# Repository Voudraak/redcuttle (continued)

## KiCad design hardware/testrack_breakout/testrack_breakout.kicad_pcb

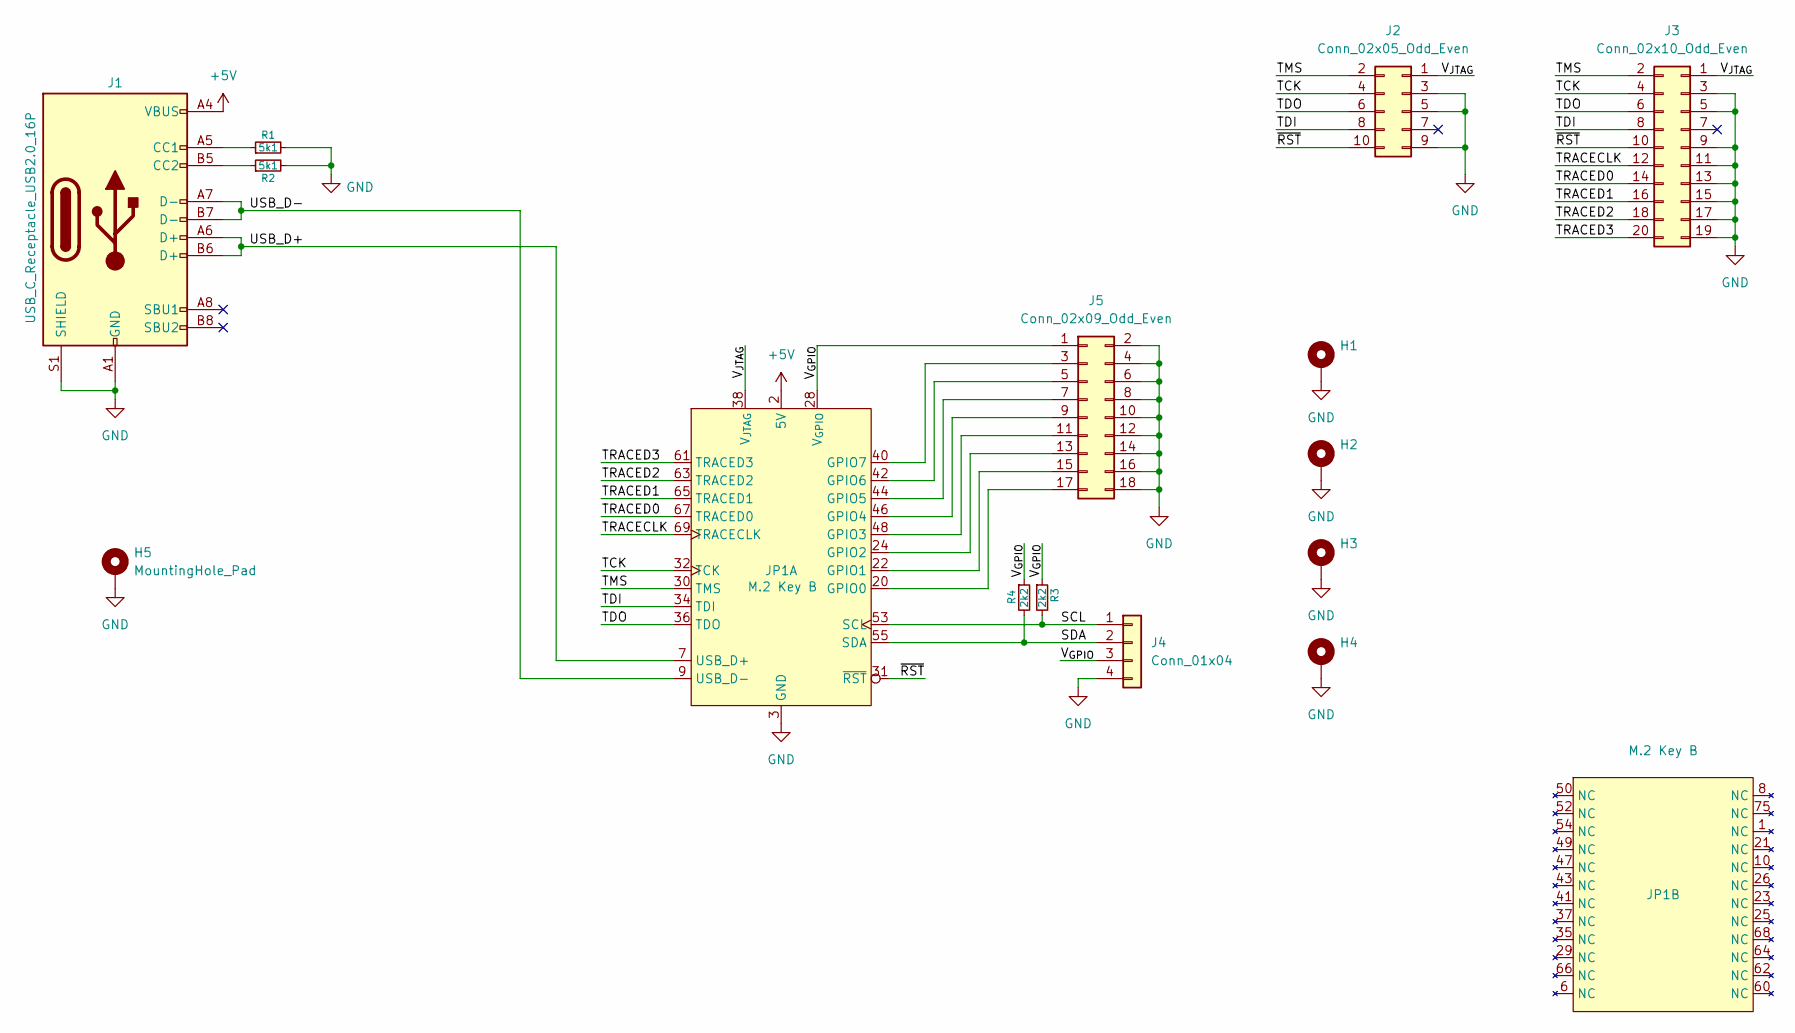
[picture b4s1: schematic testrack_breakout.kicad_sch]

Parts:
H1, H2, H3, H4: MountingHole_Pad; MountingHole_3.2mm_M3_Pad
H5: MountingHole_Pad; M2_MountingPost
J1: USB_C_Receptacle_USB2.0_16P; USB_C_Receptacle_HRO_TYPE-C-31-M-12; MPN_LCSC TYPE-C-31-M-12
J2: Conn_02x05_Odd_Even; PinHeader_2x05_P1.27mm_Vertical_SMD; MPN_FARNELL FTSH-105-01-L-DV-K-TR
J3: Conn_02x10_Odd_Even; PinHeader_2x10_P1.27mm_Vertical_SMD; MPN_FARNELL M50-3611042R
J4: Conn_01x04; JST_SH_SM04B-SRSS-TB_1x04-1MP_P1.00mm_Horizontal; MPN_FARNELL SM04B-SRSS-TB(LF)(SN)
J5: Conn_02x09_Odd_Even; PinHeader_2x09_P2.54mm_Vertical; MPN_FARNELL M20-9760942
JP1: M.2 Key B; TE_2199230-7_67_P0.5mm_Horizontal; MPN_LCSC SM3ZS067U410ABR1000
R1, R2: 5k1; R0603; MPN_FARNELL MCWR06X5101FTL
R3, R4: 2k2; R0603; MPN_FARNELL ERJU03F2201V

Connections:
+5V: J1.A4 (VBUS), J1.A9 (VBUS), J1.B4 (VBUS), J1.B9 (VBUS), JP1.2 (5V), JP1.4 (5V), JP1.70 (5V), JP1.72 (5V), JP1.74 (5V)
/SCL: J4.1, JP1.53 (SCL), R3.2
/SDA: J4.2, JP1.55 (SDA), R4.2
/TCK: J2.4, J3.4, JP1.32 (TCK)
/TDI: J2.8, J3.8, JP1.34 (TDI)
/TDO: J2.6, J3.6, JP1.36 (TDO)
/TMS: J2.2, J3.2, JP1.30 (TMS)
/TRACECLK: J3.12, JP1.69 (TRACECLK)
/TRACED0: J3.14, JP1.67 (TRACED0)
/TRACED1: J3.16, JP1.65 (TRACED1)
/TRACED2: J3.18, JP1.63 (TRACED2)
/TRACED3: J3.20, JP1.61 (TRACED3)
/USB_D+: J1.A6 (D+), J1.B6 (D+), JP1.7 (USB_D+)
/USB_D-: J1.A7 (D-), J1.B7 (D-), JP1.9 (USB_D-)
/V_{GPIO}: J4.3, J5.1, JP1.28 (V_{GPIO}), R3.1, R4.1
/V_{JTAG}: J2.1, J3.1, JP1.38 (V_{JTAG})
/~RST: J2.10, J3.10, JP1.31 (~RST)
GND: H1.1, H2.1, H3.1, H4.1, H5.1, J1.A1 (GND), J1.A12 (GND), J1.B1 (GND), J1.B12 (GND), J1.S1 (SHIELD), J2.3, J2.5, J2.9, J3.3, J3.5, J3.9, J3.11, J3.13, J3.15, J3.17, J3.19, J4.4, J5.2, J5.4, J5.6, J5.8, J5.10, J5.12, J5.14, J5.16, J5.18, JP1.3 (GND), JP1.5 (GND), JP1.11 (GND), JP1.27 (GND), JP1.33 (GND), JP1.39 (GND), JP1.45 (GND), JP1.51 (GND), JP1.57 (GND), JP1.71 (GND), JP1.73 (GND), R1.2, R2.2
unnamed: J1.A5 (CC1), R1.1
unnamed: J1.B5 (CC2), R2.1
unnamed: J5.3, JP1.40 (GPIO7)
unnamed: J5.5, JP1.42 (GPIO6)
unnamed: J5.7, JP1.44 (GPIO5)
unnamed: J5.9, JP1.46 (GPIO4)
unnamed: J5.11, JP1.48 (GPIO3)
unnamed: J5.13, JP1.24 (GPIO2)
unnamed: J5.15, JP1.22 (GPIO1)
unnamed: J5.17, JP1.20 (GPIO0)

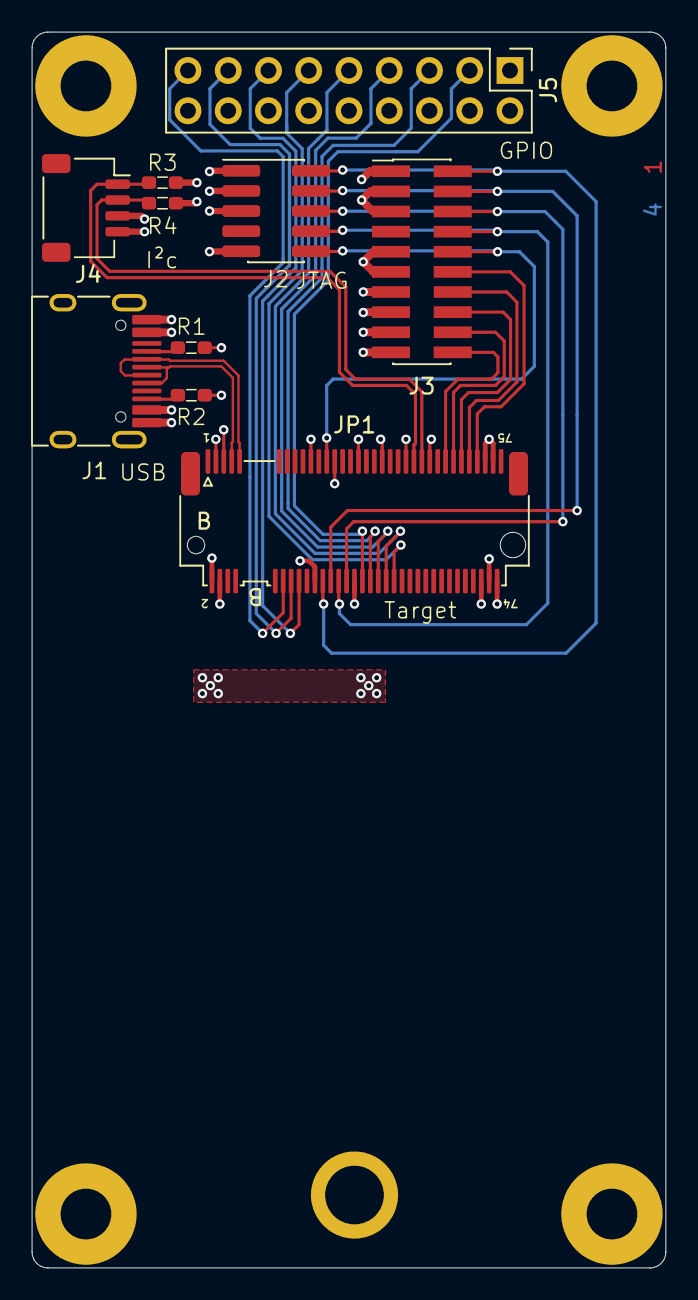
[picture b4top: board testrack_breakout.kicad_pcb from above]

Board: 4 copper layers, 40.0 x 78.0 mm, 15 parts (0 on the bottom side), 28 nets.

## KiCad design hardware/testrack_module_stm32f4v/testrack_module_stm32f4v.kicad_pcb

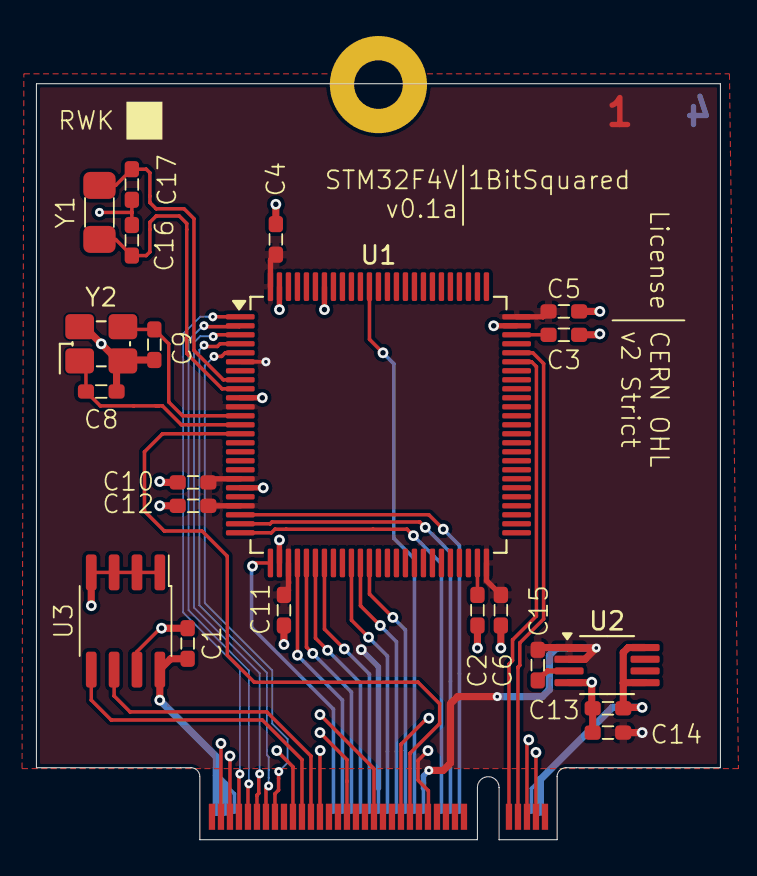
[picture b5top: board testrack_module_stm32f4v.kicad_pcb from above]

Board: 4 copper layers, 38.0 x 42.0 mm, 23 parts (0 on the bottom side), 28 nets.

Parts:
C1, C4, C5, C6, C10, C11, C12: 100n; C0603
C2, C3: 2.2u; C0603
C8, C9: 10p; C0603
C13, C14, C15: 22uF; C0603
C16, C17: 22p; C0603
H1: MountingHole_Pad; MountingHole_2.7mm_M2.5_Pad
J1: Bus_M.2_Socket_B; NGFF_B
U1: STM32F407VGTx; LQFP-100_14x14mm_P0.5mm
U2: LT1962-3.3; MSOP-8_3x3mm_P0.65mm
U3: 24AA01-I/SN; SO-8_3.9x4.9mm_P1.27mm
Y1: 32.768kHz; SMD3215
Y2: 12MHz; SMD3225

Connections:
+3.3V: C4.1, C5.1, C6.1, C10.1, C11.1, C12.1, C14.1, C15.2, J1.28 (V_{GPIO}), J1.38 (V_{JTAG}), U1.6 (VBAT), U1.11 (VDD), U1.19 (VDD), U1.22 (VDDA), U1.28 (VDD), U1.50 (VDD), U1.75 (VDD), U1.100 (VDD), U2.1 (OUT), U2.2 (SENSE)
+5V: C1.1, C13.1, J1.2 (5V), J1.4 (5V), J1.70 (5V), J1.72 (5V), J1.74 (5V), U2.5 (~SHDN), U2.8 (IN), U3.8 (VCC)
/GPIO0: J1.20 (GPIO0), U1.23 (PA0)
/GPIO1: J1.22 (GPIO1), U1.24 (PA1)
/GPIO2: J1.24 (GPIO2), U1.25 (PA2)
/GPIO3: J1.48 (GPIO3), U1.26 (PA3)
/GPIO4: J1.46 (GPIO4), U1.29 (PA4)
/GPIO5: J1.44 (GPIO5), U1.30 (PA5)
/GPIO6: J1.42 (GPIO6), U1.31 (PA6)
/GPIO7: J1.40 (GPIO7), U1.32 (PA7)
/SCL: J1.53 (SCL), U3.6 (SCL)
/SDA: J1.55 (SDA), U3.5 (SDA)
/TRACECLK: J1.69 (TRACECLK), U1.1 (PE2)
/TRACED0: J1.67 (TRACED0), U1.2 (PE3)
/TRACED1: J1.65 (TRACED1), U1.3 (PE4)
/TRACED2: J1.63 (TRACED2), U1.4 (PE5)
/TRACED3: J1.61 (TRACED3), U1.5 (PE6)
/USB_D+: J1.7 (USB_D+), U1.71 (PA12)
/USB_D-: J1.9 (USB_D-), U1.70 (PA11)
/~RST: J1.31 (~RST), U1.14 (NRST)
GND: C1.2, C2.2, C3.2, C4.2, C5.2, C6.2, C8.2, C9.2, C10.2, C11.2, C12.2, C13.2, C14.2, C16.2, C17.2, H1.1, J1.3 (GND), J1.5 (GND), J1.27 (GND), J1.33 (GND), J1.39 (GND), J1.45 (GND), J1.51 (GND), J1.57 (GND), J1.71 (GND), J1.73 (GND), U1.10 (VSS), U1.20 (VSSA), U1.27 (VSS), U1.74 (VSS), U1.94 (BOOT0), U1.99 (VSS), U2.4 (GND), U3.1 (A0), U3.2 (A1), U3.3 (A2), U3.4 (GND), U3.7 (WP), Y2.2, Y2.4
unnamed: C17.1, U1.8 (PC14), Y1.2
unnamed: C16.1, U1.9 (PC15), Y1.1
unnamed: C9.1, U1.12 (RCC_OSC_IN), Y2.3
unnamed: C8.1, U1.13 (RCC_OSC_OUT), Y2.1
unnamed: C2.1, U1.49 (VCAP_1)
unnamed: C3.1, U1.73 (VCAP_2)
unnamed: C15.1, U2.3 (BYP)

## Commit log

2025-08-28 Built a schematic for the stm32f4v target board
2025-09-13 Laid out and routed the testrack_module_stm32f4v board
2025-09-18 adding the custom schematic symbols for the m.2 connector
2025-09-18 switching the connector over to the new custom symbol and tied up loose ends
2025-09-18 initial schematic for breakout board
2025-09-26 Added the mounting hole to the target board
2025-09-26 Placed and routed the components for the breakout board
2025-10-06 Added board identification on the silkscreen
2025-10-06 Added board identification to the silkscreen
2025-10-06 Created the stm32h5 target board
2025-11-23 Variety of fixes for the STM32h5 module
2025-11-23 Designed a module for the STM32LO
2025-11-23 Started to design a board for the STM32mp153 processor
2025-11-23 Created a symbol for the MP4321 regulator
2025-11-23 Updated .gitignore to ignore schematic backups
